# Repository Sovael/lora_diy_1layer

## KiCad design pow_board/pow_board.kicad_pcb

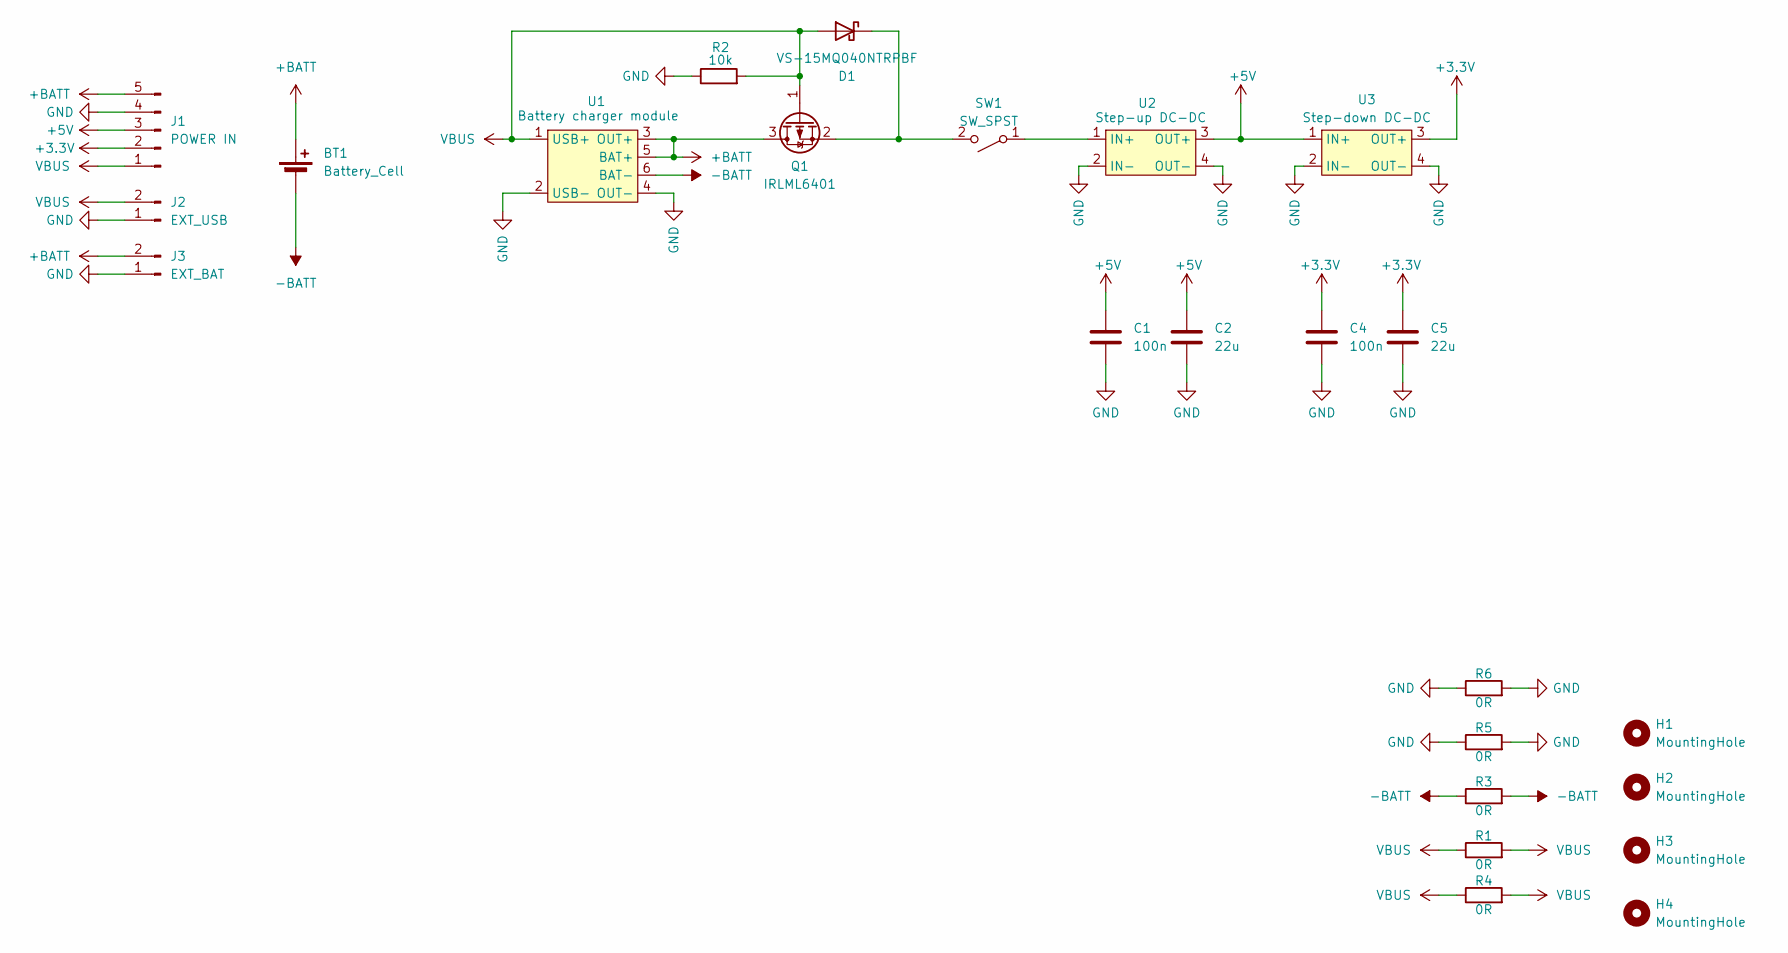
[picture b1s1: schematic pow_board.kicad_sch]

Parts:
BT1: Battery_Cell; BatteryHolder_Keystone_1042_1x18650
C1, C4: 100n; C_1206_3216Metric_Pad1.33x1.80mm_HandSolder
C2, C5: 22u; C_1206_3216Metric_Pad1.33x1.80mm_HandSolder
D1: VS-15MQ040NTRPBF; D_SMA_Handsoldering
H1, H2, H3, H4: MountingHole; MountingHole_4.3mm_M4
J1: POWER IN; PinHeader_1x05_P2.54mm_Horizontal
J2: EXT_USB; PinHeader_1x02_P2.54mm_Horizontal
J3: EXT_BAT; PinHeader_1x02_P2.54mm_Horizontal
Q1: IRLML6401; SOT-23
R1, R3, R4, R5, R6: 0R; R_1206_3216Metric_Pad1.30x1.75mm_HandSolder
R2: 10k; R_1206_3216Metric_Pad1.30x1.75mm_HandSolder
SW1: SW_SPST; PinHeader_1x02_P2.54mm_Horizontal
U1: Battery charger module; TP4056_module_typeC
U2: Step-up DC-DC; MT3608_step-up_DC-DC
U3: Step-down DC-DC; LM2596 step-down DC-DC module

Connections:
+3.3V: C4.1, C5.1, J1.2, U3.3 (OUT+)
+5V: C1.1, C2.1, J1.3, U2.3 (OUT+), U3.1 (IN+)
+BATT: BT1.1 (+), J1.5, J3.2, Q1.3 (D), U1.3 (OUT+), U1.5 (BAT+)
-BATT: BT1.2 (-), R3.1, R3.2, U1.6 (BAT-)
GND: C1.2, C2.2, C4.2, C5.2, J1.4, J2.1, J3.1, R2.1, R5.1, R5.2, R6.1, R6.2, U1.2 (USB-), U1.4 (OUT-), U2.2 (IN-), U2.4 (OUT-), U3.2 (IN-), U3.4 (OUT-)
unnamed: D1.1 (K), Q1.2 (S), SW1.2 (B)
unnamed: SW1.1 (A), U2.1 (IN+)
VBUS: D1.2 (A), J1.1, J2.2, Q1.1 (G), R1.1, R1.2, R2.2, R4.1, R4.2, U1.1 (USB+)

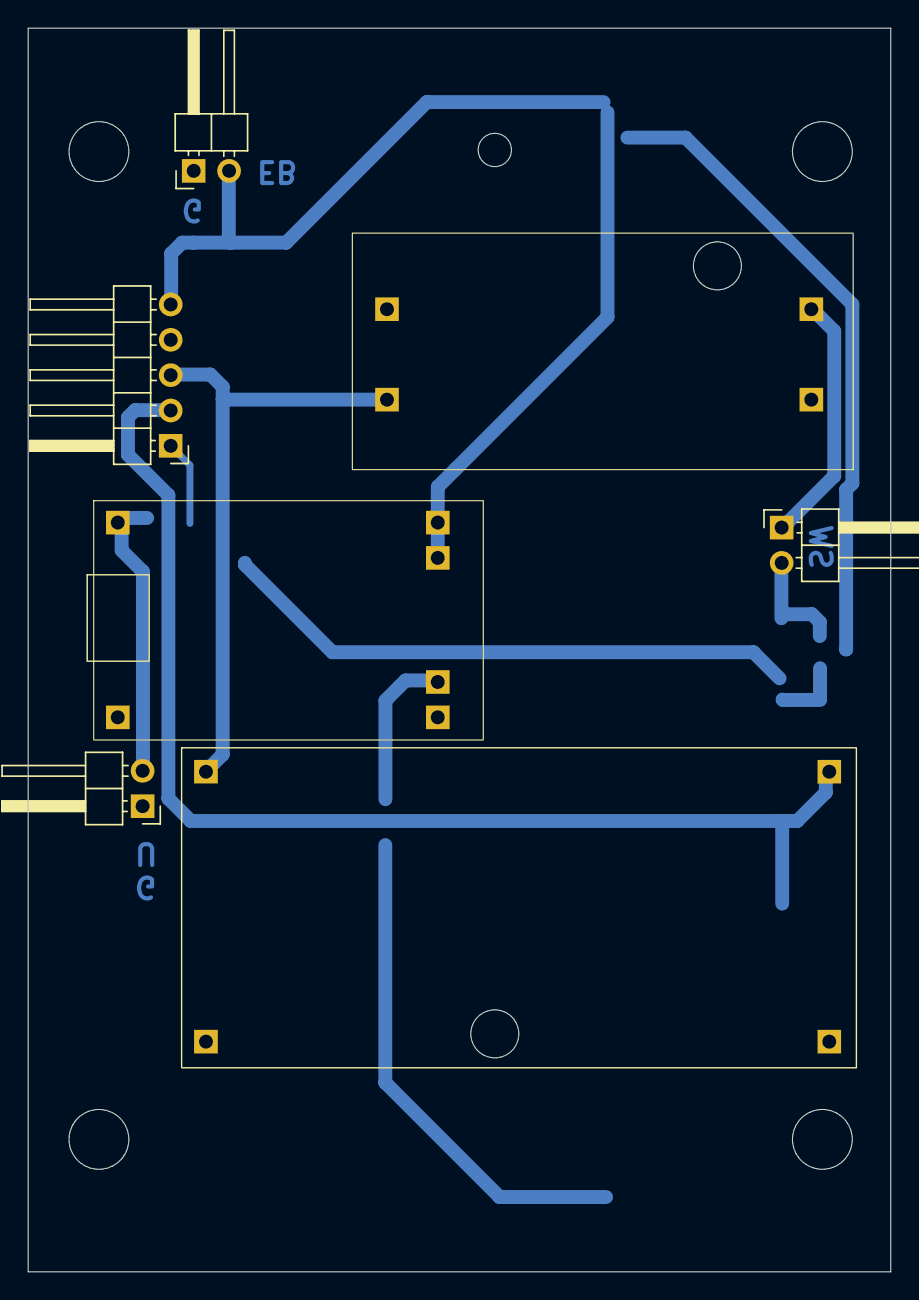
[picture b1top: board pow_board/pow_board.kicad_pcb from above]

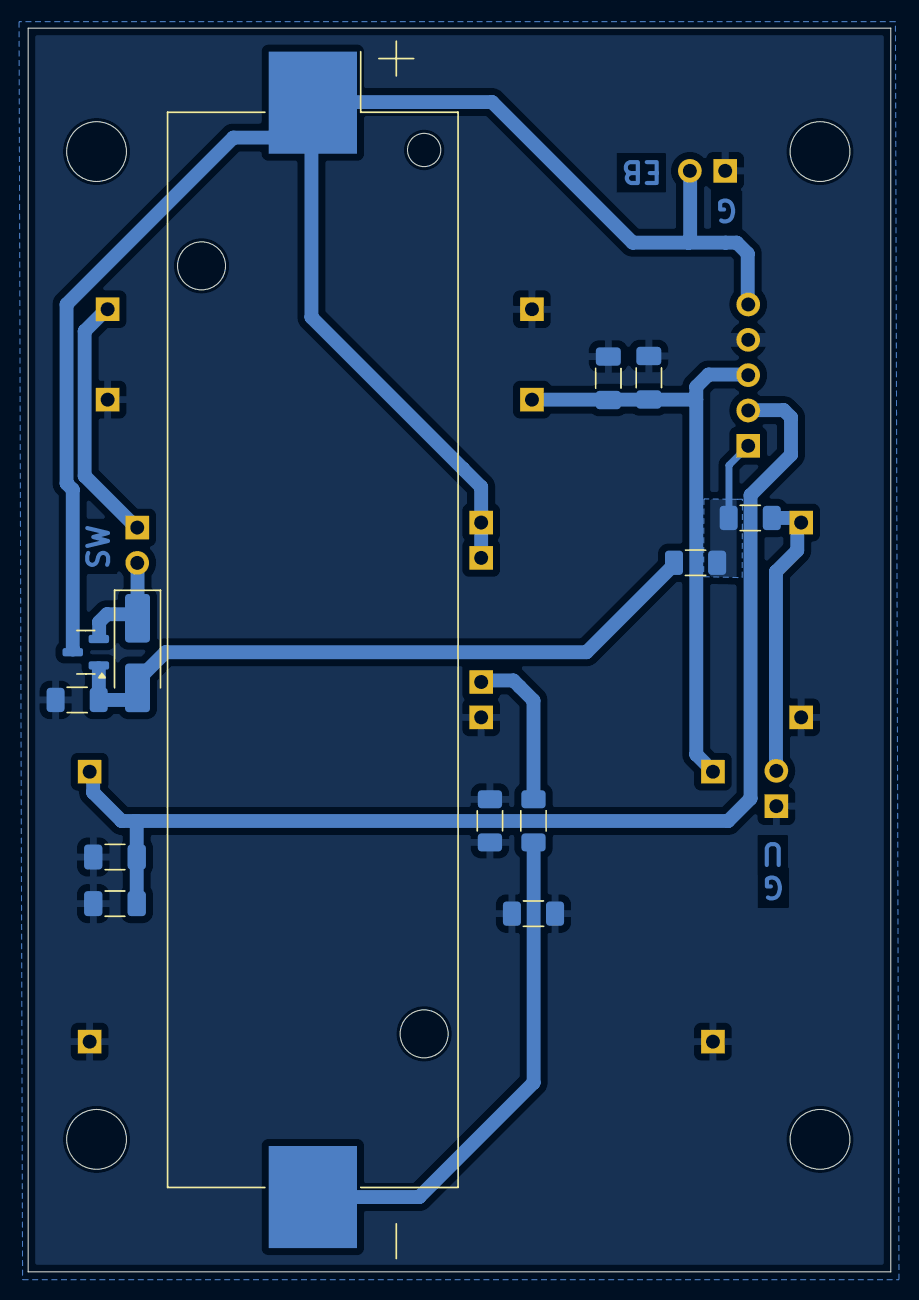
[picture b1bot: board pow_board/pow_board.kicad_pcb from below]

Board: 2 copper layers, 62.0 x 89.4 mm, 24 parts (13 on the bottom side), 8 nets.

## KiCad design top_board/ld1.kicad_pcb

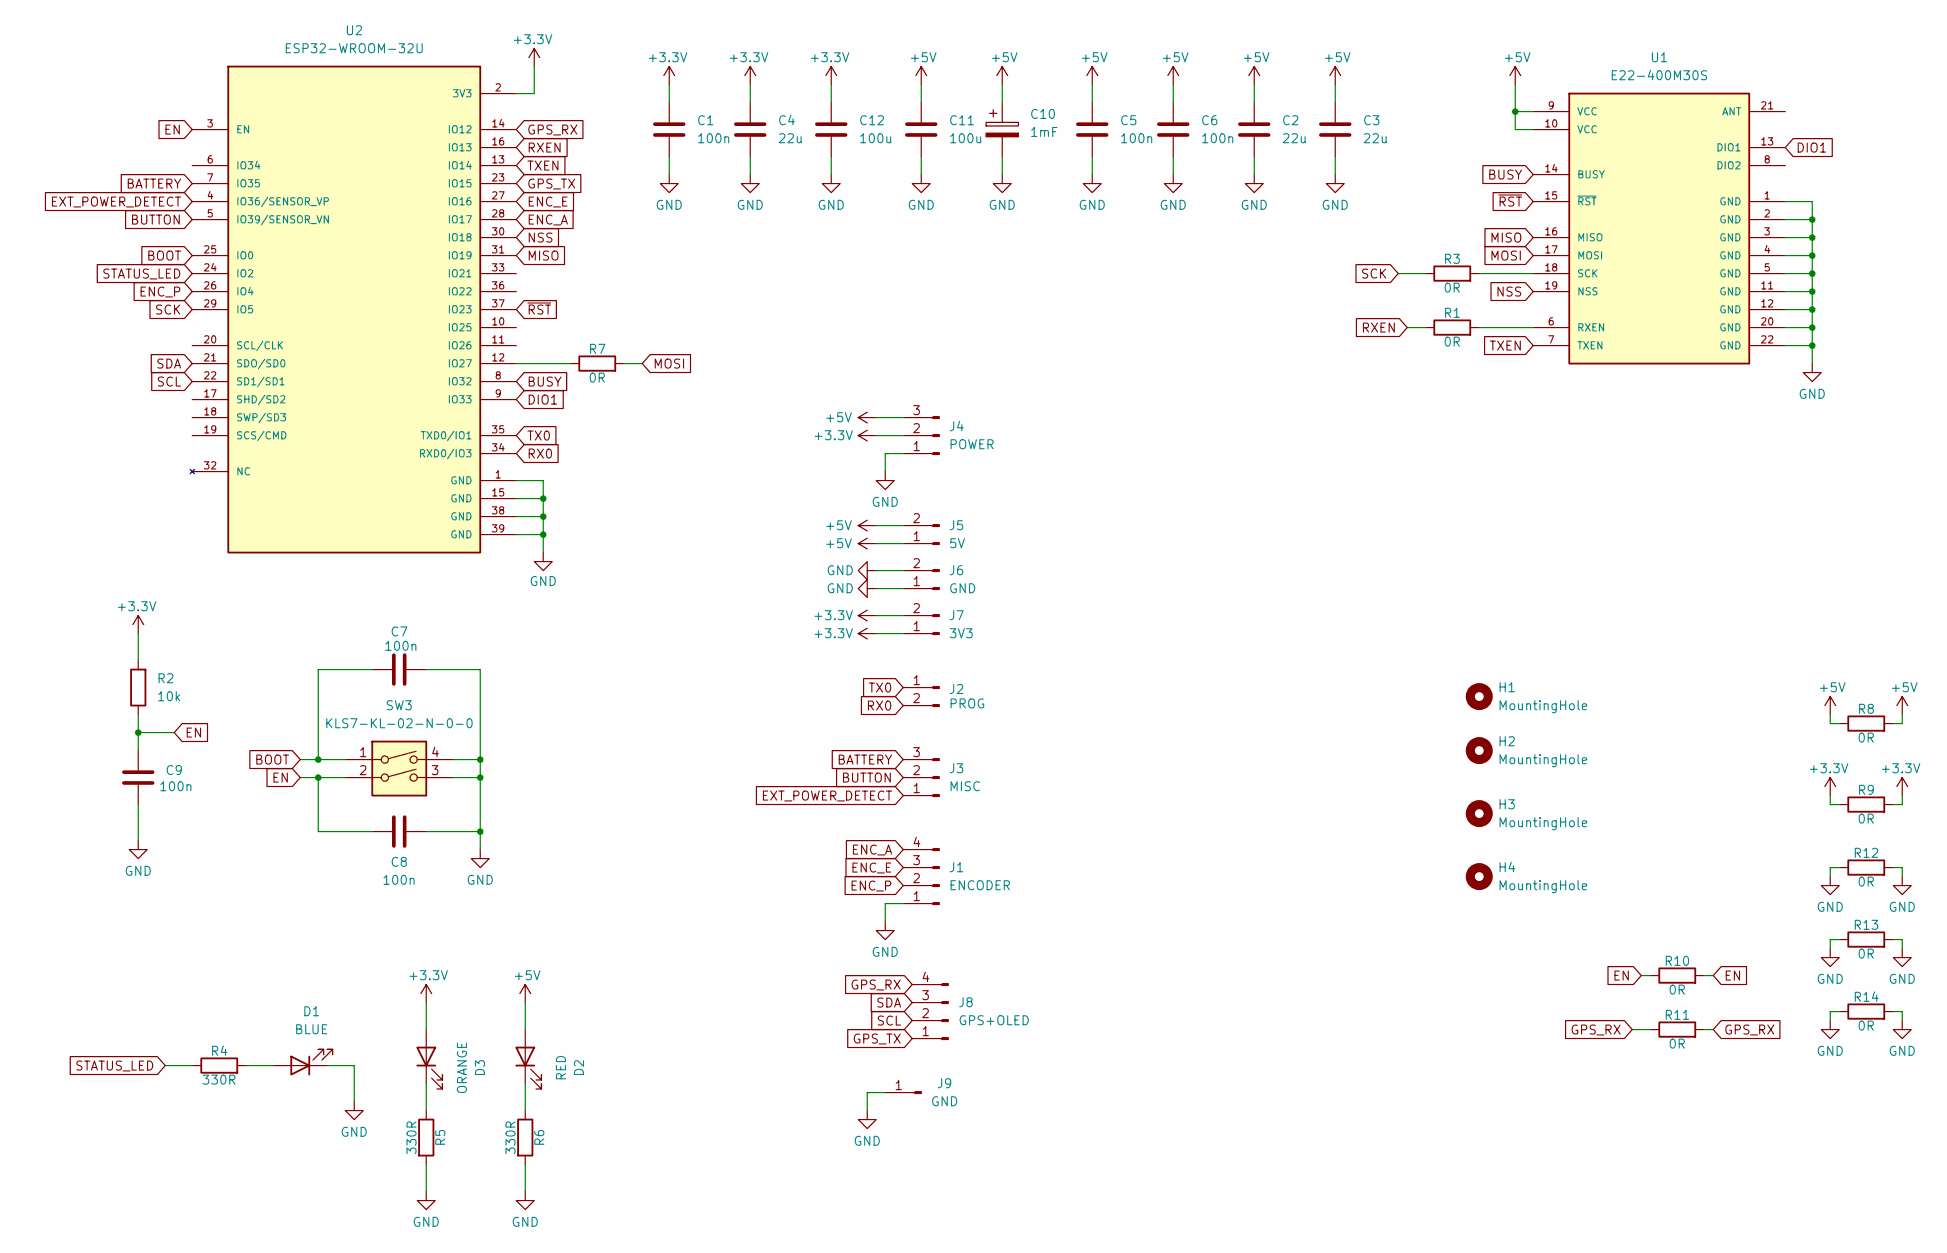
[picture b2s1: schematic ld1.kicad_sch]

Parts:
C1, C5, C6, C7, C8, C9: 100n; C_1206_3216Metric_Pad1.33x1.80mm_HandSolder
C2, C3, C4: 22u; C_1206_3216Metric_Pad1.33x1.80mm_HandSolder
C10: 1mF; CP_Elec_10x10.5
C11, C12: 100u; C_1206_3216Metric_Pad1.33x1.80mm_HandSolder
D1: BLUE; LED_1206_3216Metric_Pad1.42x1.75mm_HandSolder
D2: RED; LED_1206_3216Metric_Pad1.42x1.75mm_HandSolder
D3: ORANGE; LED_1206_3216Metric_Pad1.42x1.75mm_HandSolder
H1, H2, H3, H4: MountingHole; MountingHole_4.3mm_M4
J1: ENCODER; PinHeader_1x04_P2.54mm_Vertical
J2: PROG; PinHeader_1x02_P2.54mm_Vertical
J3: MISC; PinHeader_1x03_P2.54mm_Vertical
J4: POWER; PinHeader_1x03_P2.54mm_Vertical
J5: 5V; PinHeader_1x02_P2.54mm_Vertical
J6: GND; PinHeader_1x02_P2.54mm_Vertical
J7: 3V3; PinHeader_1x02_P2.54mm_Vertical
J8: GPS+OLED; PinHeader_1x04_P2.54mm_Vertical
J9: GND; PinHeader_1x01_P2.54mm_Vertical
R1, R3, R7, R8, R9, R10, R11, R12, R13, R14: 0R; R_1206_3216Metric_Pad1.30x1.75mm_HandSolder
R2: 10k; R_1206_3216Metric_Pad1.30x1.75mm_HandSolder
R4, R5, R6: 330R; R_1206_3216Metric_Pad1.30x1.75mm_HandSolder
SW3: KLS7-KL-02-N-0-0
U1: E22-400M30S
U2: ESP32-WROOM-32U

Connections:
+3.3V: C1.1, C4.1, C12.1, D3.2 (A), J4.2, J7.1, J7.2, R2.2, R9.1, R9.2, U2.2 (3V3)
+5V: C2.1, C3.1, C5.1, C6.1, C10.1, C11.1, D2.2 (A), J4.3, J5.1, J5.2, R8.1, R8.2, U1.9 (VCC), U1.10 (VCC)
BATTERY: J3.3, U2.7 (IO35)
BOOT: C7.2, SW3.1, U2.25 (IO0)
BUSY: U1.14 (BUSY), U2.8 (IO32)
BUTTON: J3.2, U2.5 (IO39/SENSOR_VN)
DIO1: U1.13 (DIO1), U2.9 (IO33)
EN: C8.2, C9.1, R2.1, R10.1, R10.2, SW3.2, U2.3 (EN)
ENC_A: J1.4, U2.28 (IO17)
ENC_E: J1.3, U2.27 (IO16)
ENC_P: J1.2, U2.26 (IO4)
EXT_POWER_DETECT: J3.1, U2.4 (IO36/SENSOR_VP)
GND: C1.2, C2.2, C3.2, C4.2, C5.2, C6.2, C7.1, C8.1, C9.2, C10.2, C11.2, C12.2, D1.1 (K), J1.1, J4.1, J6.1, J6.2, J9.1, R5.2, R6.2, R12.1, R12.2, R13.1, R13.2, R14.1, R14.2, SW3.3, SW3.4, U1.1 (GND), U1.2 (GND), U1.3 (GND), U1.4 (GND), U1.5 (GND), U1.11 (GND), U1.12 (GND), U1.20 (GND), U1.22 (GND), U2.1 (GND), U2.15 (GND), U2.38 (GND), U2.39 (GND)
GPS_RX: J8.4, R11.1, R11.2, U2.14 (IO12)
GPS_TX: J8.1, U2.23 (IO15)
MISO: U1.16 (MISO), U2.31 (IO19)
MOSI: R7.2, U1.17 (MOSI)
NSS: U1.19 (NSS), U2.30 (IO18)
unnamed: D1.2 (A), R4.2
unnamed: D2.1 (K), R6.1
unnamed: D3.1 (K), R5.1
unnamed: R1.2, U1.6 (RXEN)
unnamed: R3.2, U1.18 (SCK)
unnamed: R7.1, U2.12 (IO27)
RX0: J2.2, U2.34 (RXD0/IO3)
RXEN: R1.1, U2.16 (IO13)
SCK: R3.1, U2.29 (IO5)
SCL: J8.2, U2.22 (SD1/SD1)
SDA: J8.3, U2.21 (SDO/SD0)
STATUS_LED: R4.1, U2.24 (IO2)
TX0: J2.1, U2.35 (TXD0/IO1)
TXEN: U1.7 (TXEN), U2.13 (IO14)
~RST: U1.15 (~RST), U2.37 (IO23)

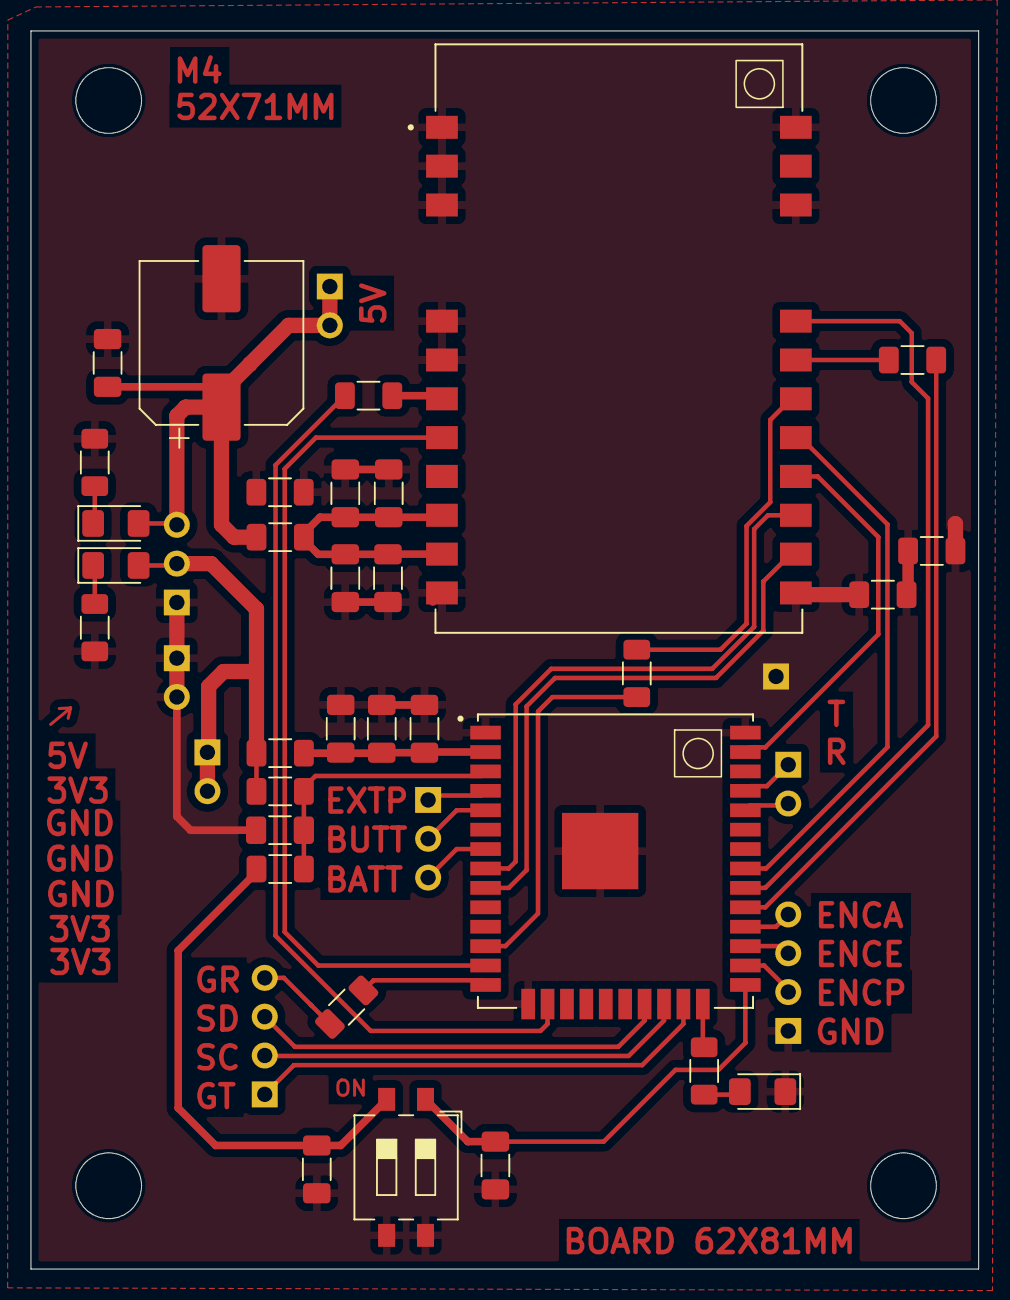
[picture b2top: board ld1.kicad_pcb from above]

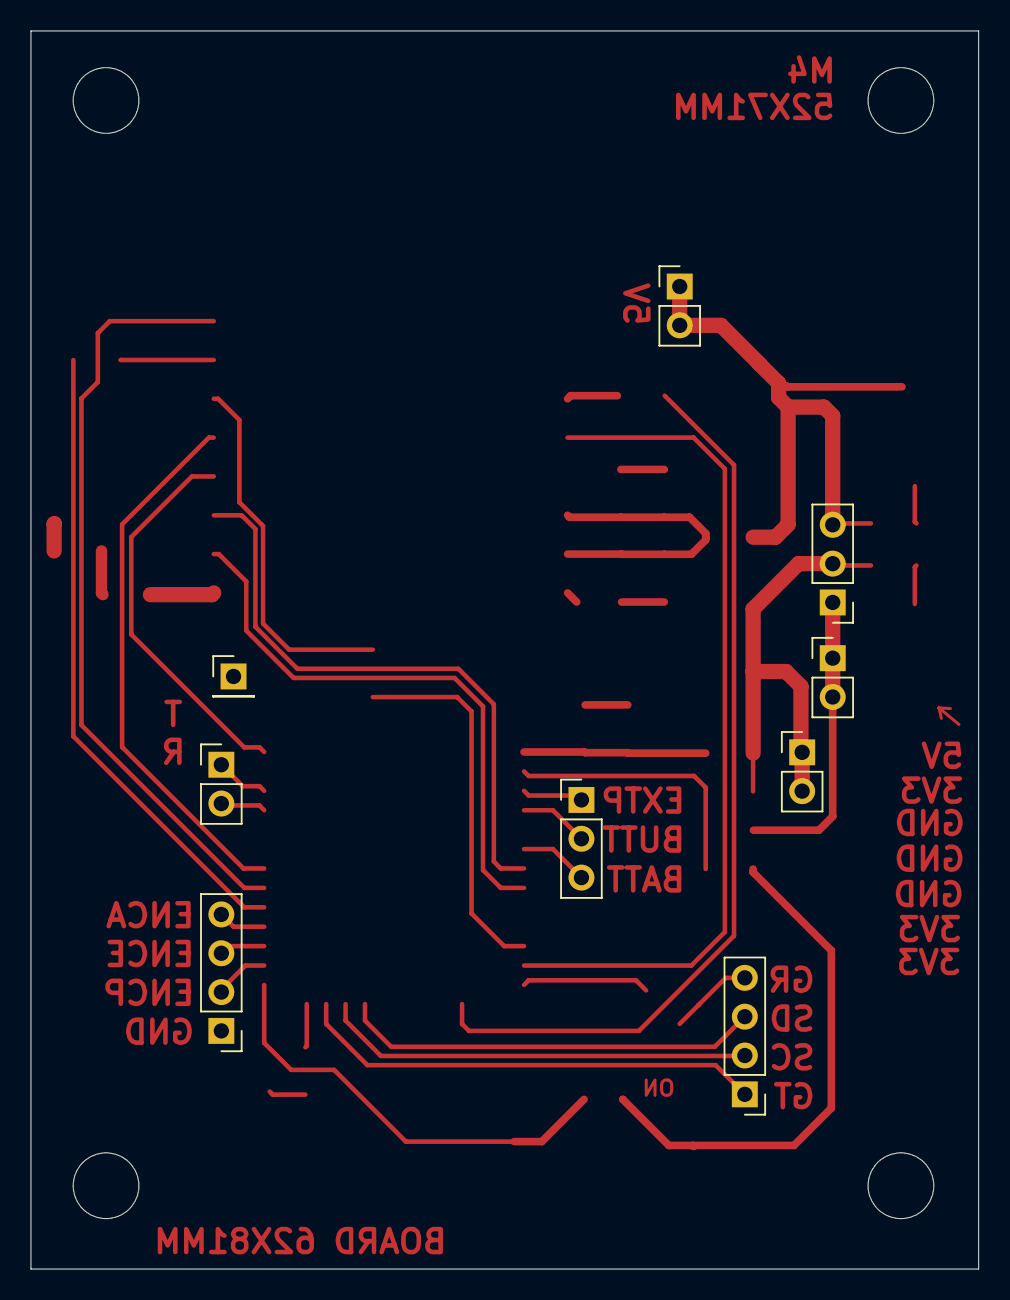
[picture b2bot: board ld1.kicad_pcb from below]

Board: 2 copper layers, 62.0 x 81.0 mm, 45 parts (9 on the bottom side), 33 nets.

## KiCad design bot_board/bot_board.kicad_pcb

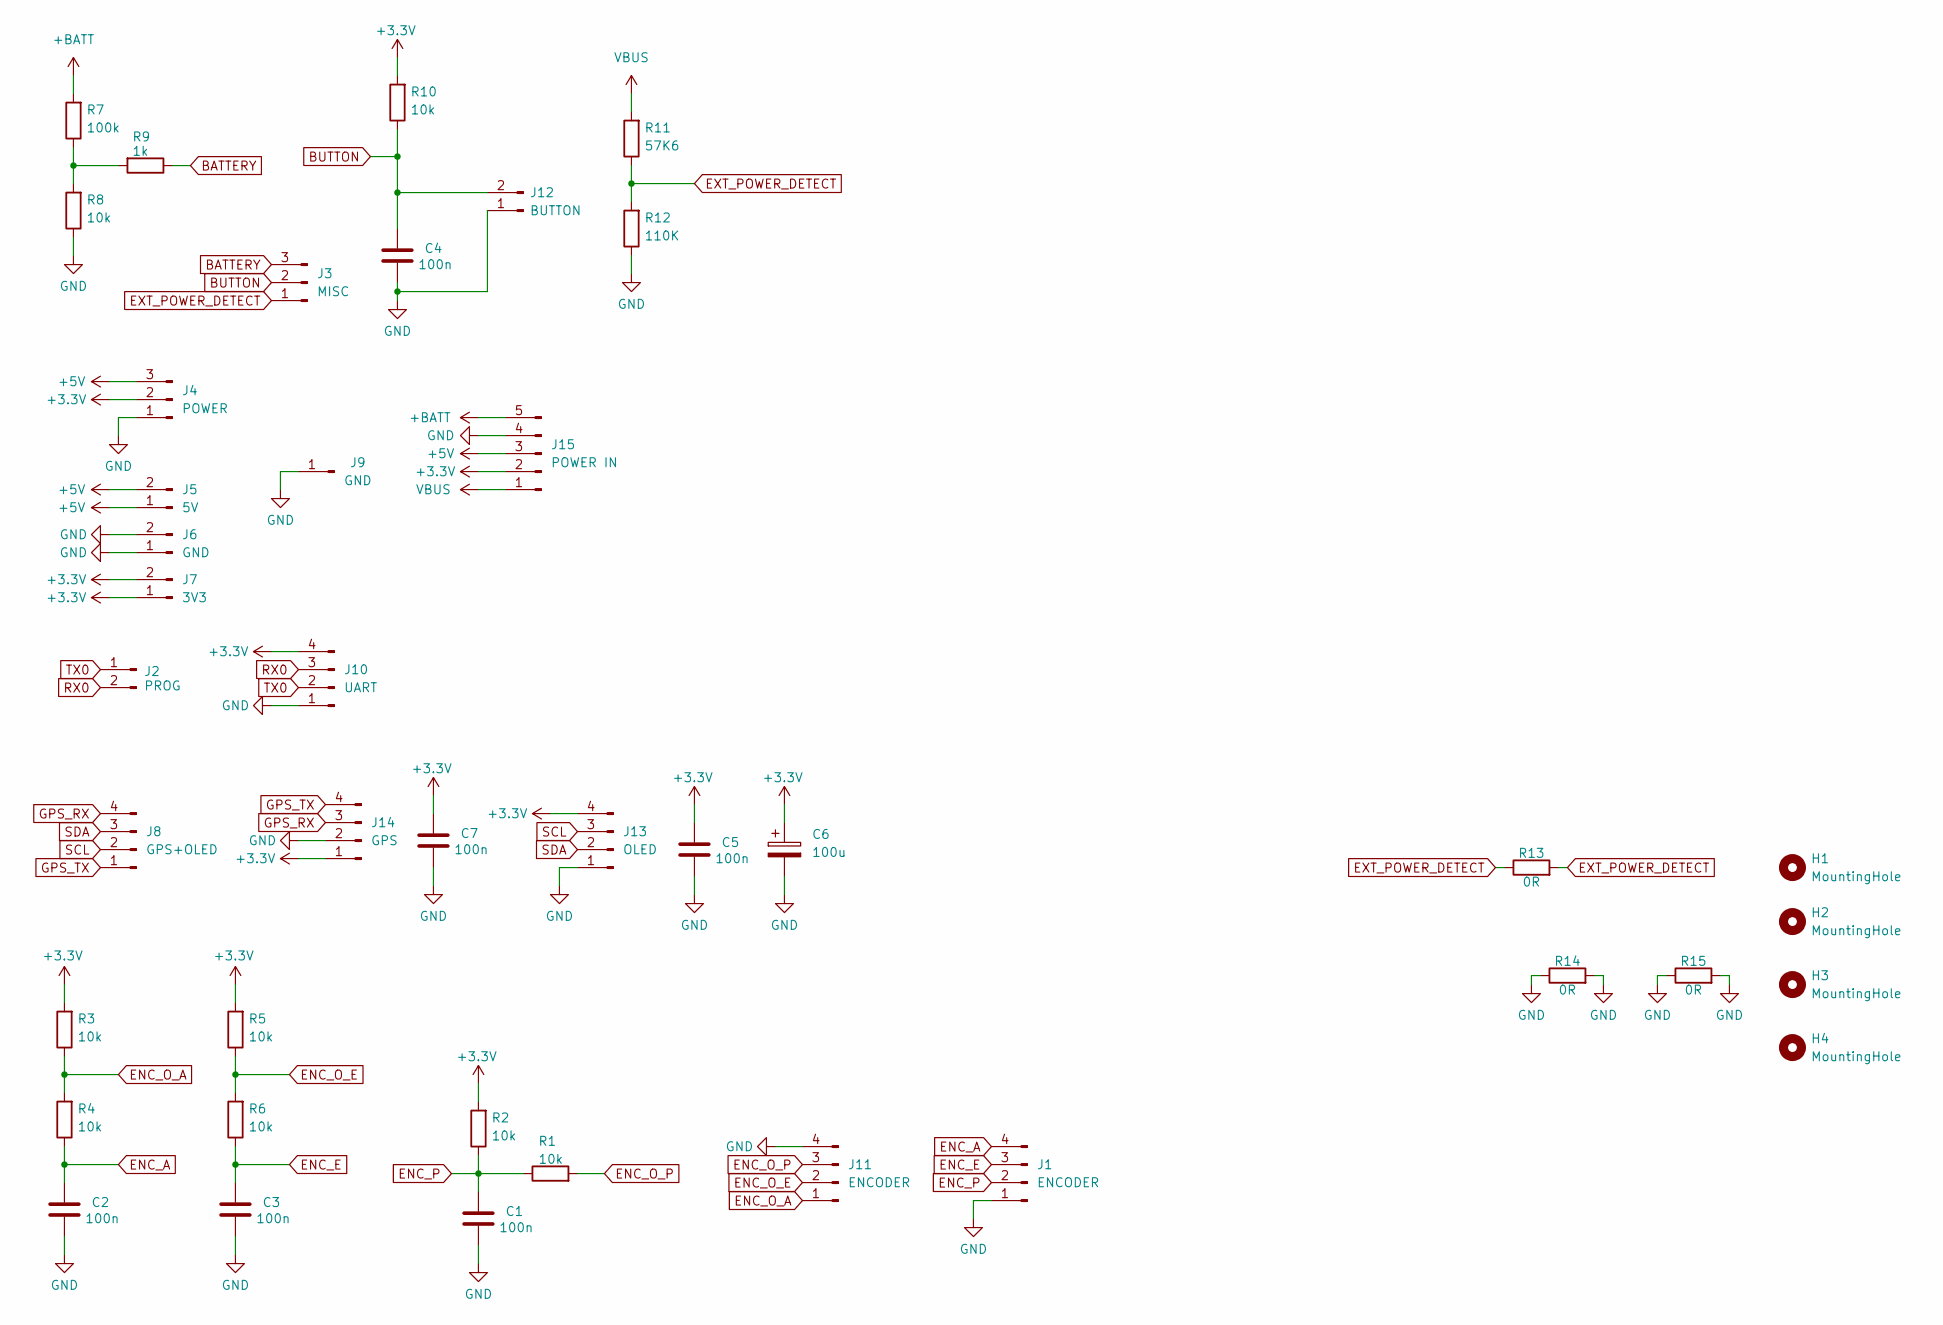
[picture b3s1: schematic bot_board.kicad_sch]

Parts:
C1, C2, C3, C4, C5, C7: 100n; C_1206_3216Metric_Pad1.33x1.80mm_HandSolder
C6: 100u; CP_EIA-3528-21_Kemet-B_Pad1.50x2.35mm_HandSolder
H1, H2, H3, H4: MountingHole; MountingHole_4.3mm_M4
J1: ENCODER; PinSocket_1x04_P2.54mm_Vertical
J2: PROG; PinSocket_1x02_P2.54mm_Vertical
J3: MISC; PinSocket_1x03_P2.54mm_Vertical
J4: POWER; PinSocket_1x03_P2.54mm_Vertical
J5: 5V; PinSocket_1x02_P2.54mm_Vertical
J6: GND; PinSocket_1x02_P2.54mm_Vertical
J7: 3V3; PinSocket_1x02_P2.54mm_Vertical
J8: GPS+OLED; PinSocket_1x04_P2.54mm_Vertical
J9: GND; PinSocket_1x01_P2.54mm_Vertical
J10: UART; PinHeader_1x04_P2.54mm_Horizontal
J11: ENCODER; PinHeader_1x04_P2.54mm_Horizontal
J12: BUTTON; PinHeader_1x02_P2.54mm_Horizontal
J13: OLED; PinHeader_1x04_P2.54mm_Horizontal
J14: GPS; PinHeader_1x04_P2.54mm_Horizontal
J15: POWER IN; PinHeader_1x05_P2.54mm_Horizontal
R1, R2, R3, R4, R5, R6, R8, R10: 10k; R_1206_3216Metric_Pad1.30x1.75mm_HandSolder
R7: 100k; R_1210_3225Metric_Pad1.30x2.65mm_HandSolder
R9: 1k; R_1206_3216Metric_Pad1.30x1.75mm_HandSolder
R11: 57K6; R_1210_3225Metric_Pad1.30x2.65mm_HandSolder
R12: 110K; R_1206_3216Metric_Pad1.30x1.75mm_HandSolder
R13, R14, R15: 0R; R_1206_3216Metric_Pad1.30x1.75mm_HandSolder

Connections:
+3.3V: C5.1, C6.1, C7.1, J4.2, J7.1, J7.2, J10.4, J13.4, J14.1, J15.2, R2.2, R3.2, R5.2, R10.2
+5V: J4.3, J5.1, J5.2, J15.3
+BATT: J15.5, R7.2
BATTERY: J3.3, R9.1
BUTTON: C4.1, J3.2, J12.2, R10.1
ENC_A: C2.1, J1.4, R4.1
ENC_E: C3.1, J1.3, R6.1
ENC_O_A: J11.1, R3.1, R4.2
ENC_O_E: J11.2, R5.1, R6.2
ENC_O_P: J11.3, R1.2
ENC_P: C1.1, J1.2, R1.1, R2.1
EXT_POWER_DETECT: J3.1, R11.1, R12.2, R13.1, R13.2
GND: C1.2, C2.2, C3.2, C4.2, C5.2, C6.2, C7.2, J1.1, J4.1, J6.1, J6.2, J9.1, J10.1, J11.4, J12.1, J13.1, J14.2, J15.4, R8.1, R12.1, R14.1, R14.2, R15.1, R15.2
GPS_RX: J8.4, J14.3
GPS_TX: J8.1, J14.4
unnamed: R7.1, R8.2, R9.2
RX0: J2.2, J10.3
SCL: J8.2, J13.3
SDA: J8.3, J13.2
TX0: J2.1, J10.2
VBUS: J15.1, R11.2

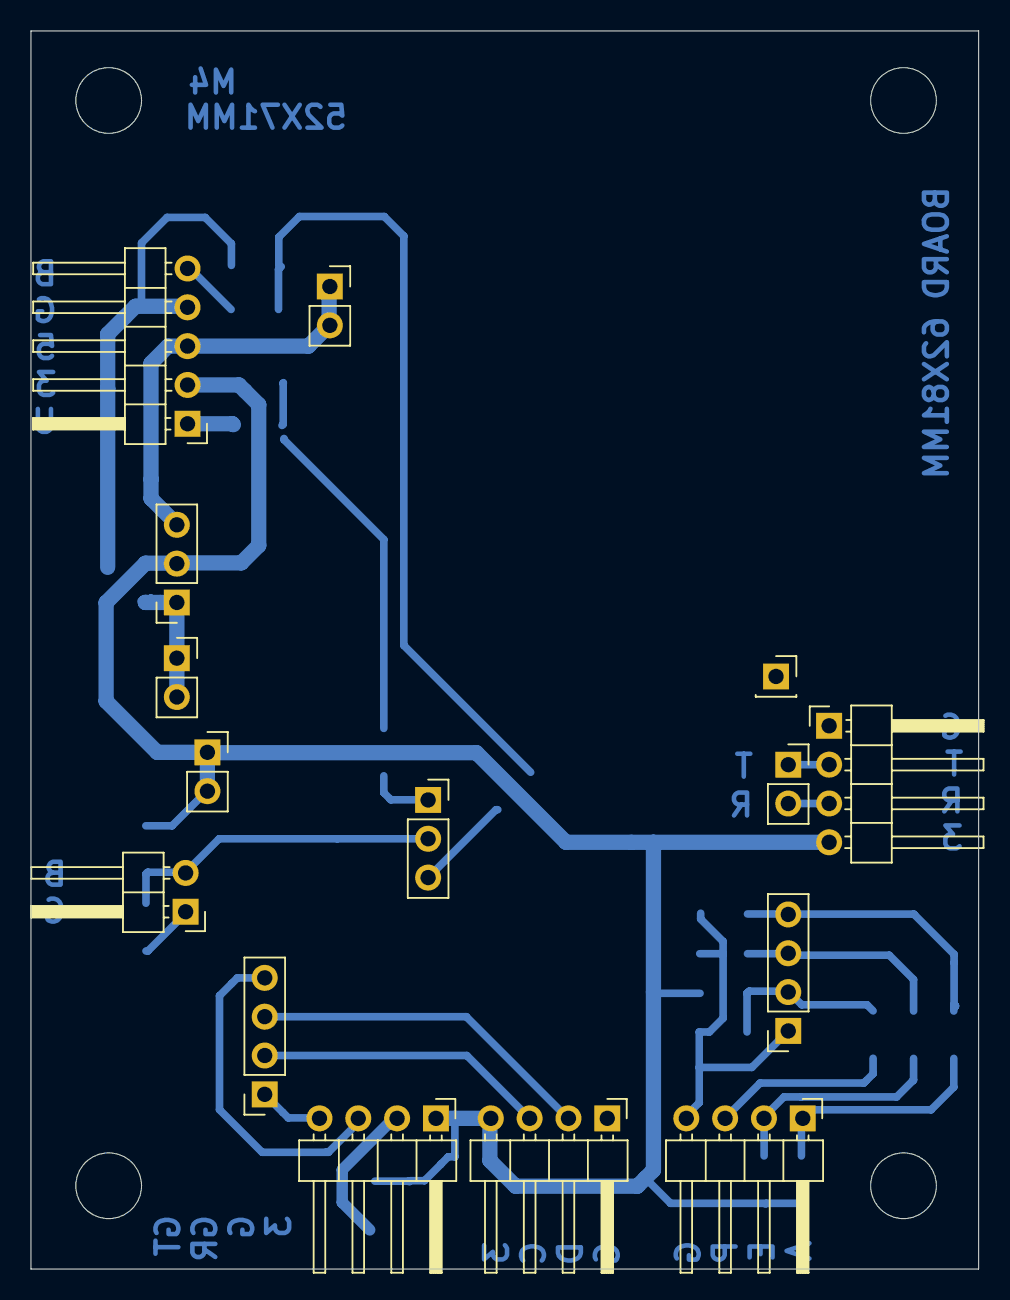
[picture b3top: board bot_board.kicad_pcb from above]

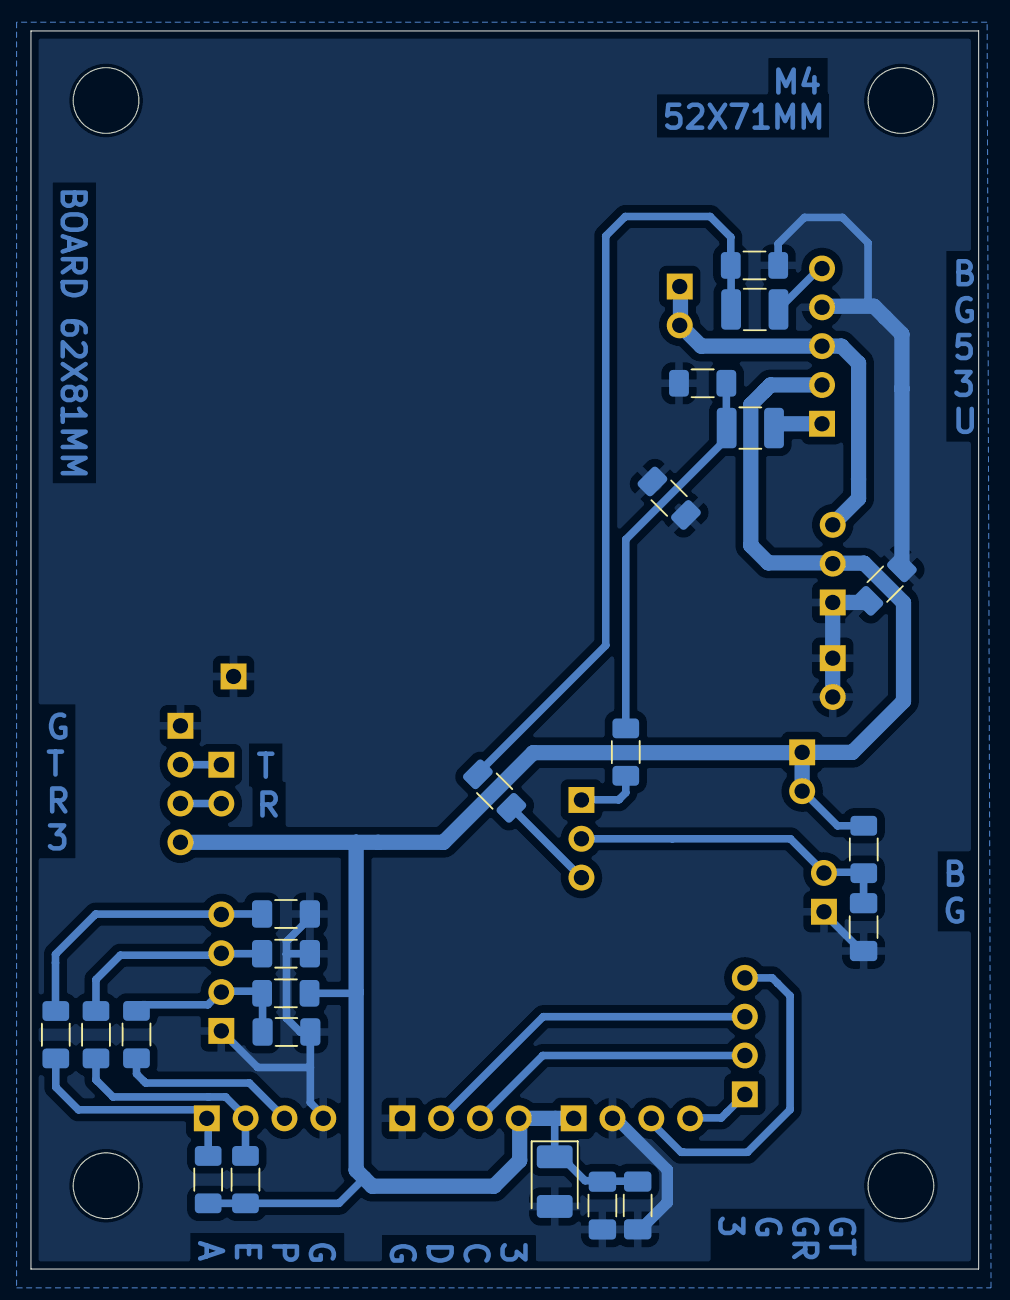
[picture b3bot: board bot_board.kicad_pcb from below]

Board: 2 copper layers, 62.0 x 81.0 mm, 41 parts (22 on the bottom side), 21 nets.

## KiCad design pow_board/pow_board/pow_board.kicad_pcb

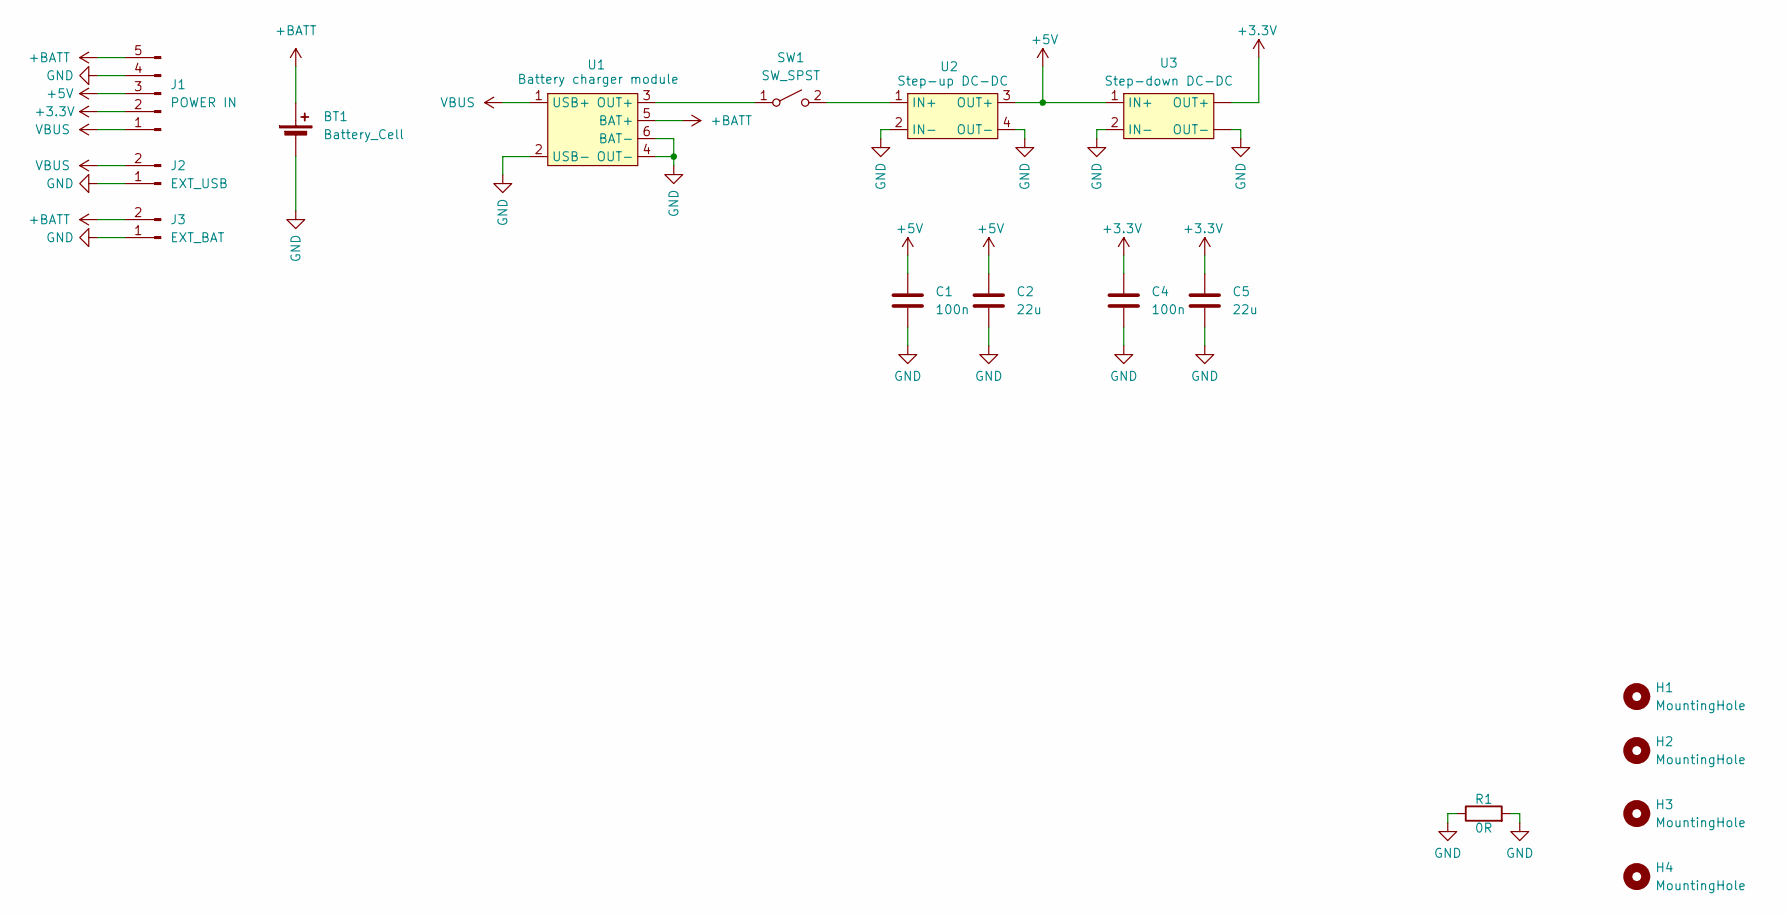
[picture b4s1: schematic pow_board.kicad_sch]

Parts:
BT1: Battery_Cell; BatteryHolder_Keystone_1042_1x18650
C1, C4: 100n; C_1206_3216Metric_Pad1.33x1.80mm_HandSolder
C2, C5: 22u; C_1206_3216Metric_Pad1.33x1.80mm_HandSolder
H1, H2, H3, H4: MountingHole; MountingHole_3.2mm_M3
J1: POWER IN; PinHeader_1x05_P2.54mm_Horizontal
J2: EXT_USB; PinSocket_1x02_P2.54mm_Horizontal
J3: EXT_BAT; PinSocket_1x02_P2.54mm_Horizontal
R1: 0R; R_1206_3216Metric_Pad1.30x1.75mm_HandSolder
SW1: SW_SPST; PinHeader_1x02_P2.54mm_Horizontal
U1: Battery charger module; TP4056_module_typeC
U2: Step-up DC-DC; MT3608_step-up_DC-DC
U3: Step-down DC-DC

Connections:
+3.3V: C4.1, C5.1, J1.2, U3. (OUT+)
+5V: C1.1, C2.1, J1.3, U2.3 (OUT+), U3.1 (IN+)
+BATT: BT1.1 (+), J1.5, J3.2, U1.5 (BAT+)
GND: BT1.2 (-), C1.2, C2.2, C4.2, C5.2, J1.4, J2.1, J3.1, R1.1, R1.2, U1.2 (USB-), U1.4 (OUT-), U1.6 (BAT-), U2.2 (IN-), U2.4 (OUT-), U3. (OUT+), U3.2 (IN-)
unnamed: SW1.1 (A), U1.3 (OUT+)
unnamed: SW1.2 (B), U2.1 (IN+)
VBUS: J1.1, J2.2, U1.1 (USB+)

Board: 2 copper layers, 16 parts (1 on the bottom side), 7 nets, no tracks yet.

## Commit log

2024-05-01 Main board done. Can work standalone, but may get an underlying power-and-control-board.
2024-05-01 Fixed pinsocket connector, fixed missing connectors footprints
2024-05-01 Added GND pin for better return current path when using underlying board
2024-05-02 Added 100u caps
2024-05-02 Separation for top and bottom boards
2024-05-02 Slight fixes in top board, populating schematic for bot board
2024-05-02 Bot board done. Pow board started
2024-05-02 pow board start
2024-05-02 Boards done, composition done
2024-05-02 Fixed modules sizes
2024-05-03 Assembly done, changing to M4 in next commit
2024-05-03 Recovering after git fatal error. Changed M3 to M4
